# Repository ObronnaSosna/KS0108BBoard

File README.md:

# KS0108B Arduino Board Program

Board schematics to use with KS0108B Arduino and KS0108B Simulator

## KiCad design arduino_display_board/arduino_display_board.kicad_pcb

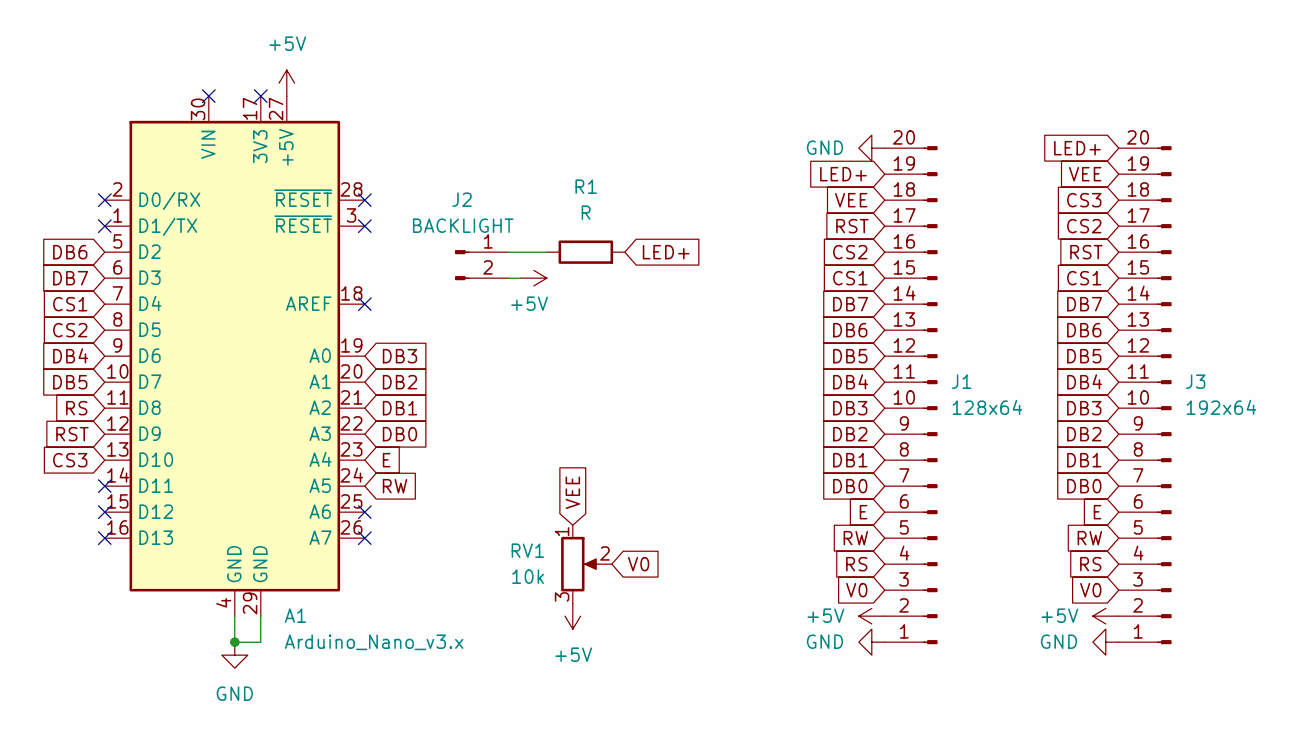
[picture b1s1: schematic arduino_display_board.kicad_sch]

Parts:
A1: Arduino_Nano_v3.x; Arduino_Nano
J1: 128x64; PinSocket_1x20_P2.54mm_Vertical
J2: BACKLIGHT; PinHeader_1x02_P2.54mm_Vertical
J3: 192x64; PinSocket_1x20_P2.54mm_Vertical
R1: R; R_Axial_DIN0204_L3.6mm_D1.6mm_P2.54mm_Vertical
RV1: 10k; Potentiometer_Alps_RK163_Single_Horizontal

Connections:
+5V: A1.27 (+5V), J1.2, J2.2, J3.2, RV1.3
CS1: A1.7 (D4), J1.15, J3.15
CS2: A1.8 (D5), J1.16, J3.17
CS3: A1.13 (D10), J3.18
DB0: A1.22 (A3), J1.7, J3.7
DB1: A1.21 (A2), J1.8, J3.8
DB2: A1.20 (A1), J1.9, J3.9
DB3: A1.19 (A0), J1.10, J3.10
DB4: A1.9 (D6), J1.11, J3.11
DB5: A1.10 (D7), J1.12, J3.12
DB6: A1.5 (D2), J1.13, J3.13
DB7: A1.6 (D3), J1.14, J3.14
E: A1.23 (A4), J1.6, J3.6
GND: A1.4 (GND), A1.29 (GND), J1.1, J1.20, J3.1
LED+: J1.19, J3.20, R1.2
unnamed: J2.1, R1.1
RS: A1.11 (D8), J1.4, J3.4
RST: A1.12 (D9), J1.17, J3.16
RW: A1.24 (A5), J1.5, J3.5
V0: J1.3, J3.3, RV1.2
VEE: J1.18, J3.19, RV1.1

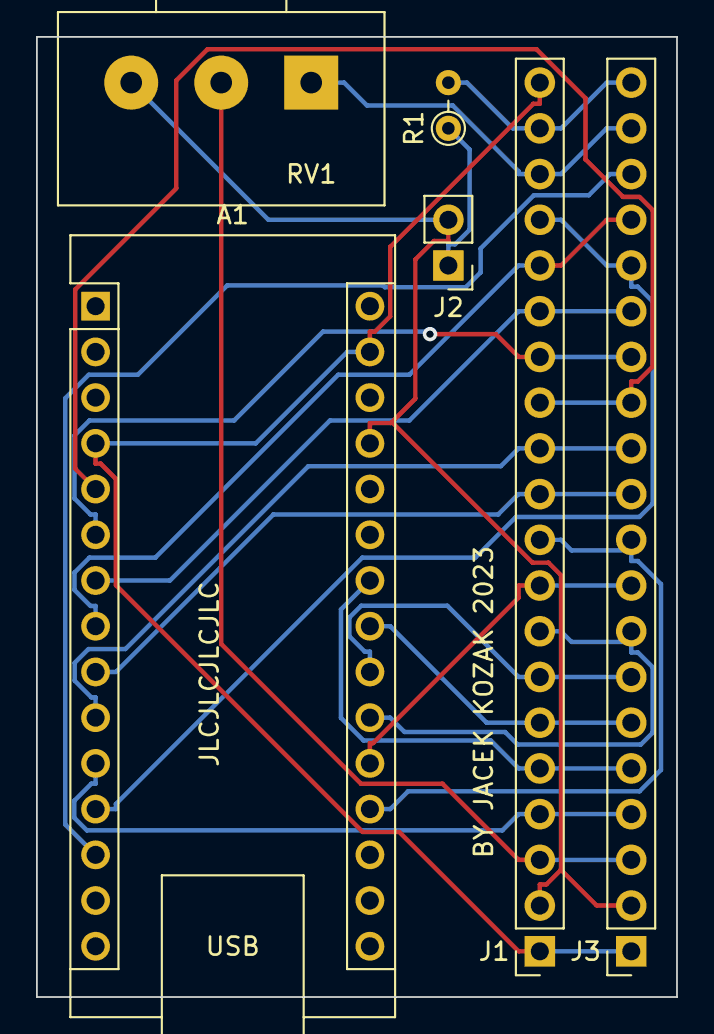
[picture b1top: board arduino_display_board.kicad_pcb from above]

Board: 2 copper layers, 35.6 x 53.3 mm, 6 parts (0 on the bottom side), 21 nets.

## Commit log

2023-11-20 initial
2024-05-10 added readme and license
